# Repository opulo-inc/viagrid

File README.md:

# Viagrid
<br><br>

ViaGrid is a set of standardized PCB blank templates with pre-embedded vias in grid patterns, allowing for rapid 2 layer PCB prototyping and low-volume manufacturing, even at home. Instead of placing vias ad-hoc during routing, existing grid vias are assigned nets as needed and routed to in-place. Unused vias can remain part of the ground pour, orphaned by assigning an unused net, or converted to simple drilled holes. Viagrid blanks can be processed with a UV DPSS laser engravers, MLL machine and chemical etching, or with traditional CNC milling.<br><br>

> [!NOTE]
> Viagrid is still in development and is constantly evolving! If you wish to start creating PCBs based on a viagrid template who's status is not Complete in the table below, come and visit the #viagrid channel in the [Opulo Discord](https://discordapp.com/invite/TCwy6De) and ask for the latest version of the template you want to work with!
>
<br>**Currently, only the 9055 Standard blank is complete.** Other blank sizes and densities are planned:<br><br>

| Blank Name  | Status | Vias | Dimensions | Mounting ⌀ | Enclosure | Preview |
| ------------- | ------------- | ------------- | ------------- | ------------- | ------------- | ------------- |
| [ViaGrid 9055 Standard](https://github.com/opulo-inc/viagrid/tree/main/VIAGRID%20BLANK%20FILES/9055%20STANDARD) | Complete  | 180 | 90 x 55mm | Yes | Hammond 1591XXB Series | [Click Here](VIAGRID%20BLANK%20FILES/9055%20STANDARD/VIAGRID_9055_STANDARD.png) |
| ViaGrid 9055 Dense | Planned | TBD | 90 x 55mm | Yes | Hammond 1591XXB Series | Not Yet Available |
| [ViaGrid 6034 Standard](https://github.com/opulo-inc/viagrid/tree/main/VIAGRID%20BLANK%20FILES/6034%20STANDARD) | Complete | 82 | 60 x 34mm | Yes | Hammond 1551K/L Series | [Click Here](VIAGRID%20BLANK%20FILES/6034%20STANDARD/VIAGRID_6034_STANDARD.png) |
| ViaGrid 6034 Dense | Planned | TBD | 60 x 34mm | Yes | Hammond 1551K/L Series | Not Yet Available |
| ViaGrid Pi Hat | Planned | TBD | 65 x 56.5mm | Yes | Various Existing | Not Yet Available |
| ViaGrid Arduino Shield | Planned | TBD | 66.04 x 53.34mm | Yes | Various Existing | Not Yet Available |
| ViaGrid Guitar Pedal | Planned | TBD | 120 x 70mm | Yes | TBD | Not Yet Available |

<br>**Below is a preview of the ViaGrid 9055 Standard blank describing some quality of life features:**<br>
<br>

## Table of Contents
[File Prep](#file-prep)<br>
[Design](#design)<br>
[File Export](#file-export)<br>
[Fabrication Methods](#fabrication-methods)
<br><br>

When doing board layout, you drop your components onto the Viagrid template file. This shows you where the Viagrid blank already has vias embedded. When routing your board, simply drop your vias only where the Viagrid blank already has them.

When it comes time to fabricate your board, you only have to remove copper from the top and bottom layers, effectively deciding which net the vias are part of. This process can be done using UV DPSS lasers, chemical etching or CNC machining.

## File Prep

> [!NOTE]
> Viagrid has templates and instructions for only KiCAD and Eagle at the moment.

## Design

1. Design your schematic in KiCAD like you usually would. Assign footprints.
2. Before opening the .kicad_pcb file associated with your project, copy the `viagrid-template.kicad_pcb` file into your KiCAD project directory, and rename it to replace the default one.
3. Open the newly renamed `.kicad_pcb` file in KiCAD. The `User1` layer shows the location of the vias on the Viagrid blank, and the outer bounds of the usable area.
4. Set your board settings for best results:
   1. Vias: 1.5mm ring, 0.3mm drill
   2. Traces: no smaller than 0.2mm
   3. Copper pour: at least 0.3mm clearance
5. Route your board like you normally would.

## File Export

1. File -> Plot
2. When exporting, we only care about the front and back copper layers, and the front and back mask layers. Select these.
3. Export files as .DXF

## Fabrication Methods

[UV DPSS Laser Engraving](#uv-dpss-laser-engraving)<br>
[MLL & Chemical Etching](#chemical-etching)<br>
[CNC Machining](#cnc-machining)<br>
<br/>

### UV DPSS Laser Engraving

> [!WARNING]
> Lasers can damage or destroy your eyesight in milliseconds if you're not careful. Always wear certified, trustworthy eye protection MATCHED TO YOUR SPECIFIC LASER WAVELENGTH AND POWER and obtained from a reputable source such as ThorLabs when working with or around your laser. Keep all guards and protective filters in place when the laser is active, and follow all safe operating instructions provided by the manufacturer of your machine.

> [!WARNING]
> Lasers can ignite a surprising range of materials quickly and without warning, resulting in dangerous fires!  Never leave your laser unattended! Always keep a carbon dioxide fire extinguisher near your machine that's easily accessible!

Viagrid boards can be easily and autonomously cut using a UV DPSS (Diode Pumped Solid State) laser. These are commercially available and getting cheaper by the year. These instructions were prepared using a [Commarker Omni 1 (5W)](https://store.commarker.com/products/omni-1-uv-laser-engraver) however the same company has recently released a similar machine that is fully enclosed, called the [Omni X](https://store.commarker.com/products/omni-x-uv-laser-engraver).

> [!NOTE]
> We are asking a lot of this laser for this application. Any slight alignment error can result in inconsistent results across the work area.
> In my case, the laser galvo head was ever so slightly at an angle relative to the work area, which caused my cuts to be clean in one area, but barely work in others.
> To rectify this, I recommend barely loosening the three screws holding the galvo head onto the laser body, rotating the head until both sides are the same height from the work area, then tightening back down. I saw marked improvement to cutting performance after performing this adjustment.

#### Laser Prep

1. Print and assemble the alignment jig. Refer to the BOM in the relevant jig folder in this repository.
2. Mount to the laser base using M5x16mm bolts.
3. Mount a viagrid blank into the jig.
4. Connect the laser to your computer and follow manufacturer instructions for setup in Lightburn, including setting focus, scale, and Z-height.
5. Open the `viagrid.lbrn2` file in Lightburn.
6. Click the purple rectangle showing the outline of the viagrid copper pour (on layer 25).
7. Check `Output` next to layer 25, and then click the frame button.
8. Your laser should now be tracing this rectangle. Confirm that you see it tracing in a blue color. Use the visualization panel that comes with the laser if needed.
9. It's likely that the tracing is very far off from where the actual viagrid board is. If so, select the purple and brown rectangles and move them on the work area and frame again until you're within a few millimeters of the board's actual location.
10. Select the purple and brown rectangles, right click, and lock them.
11. Loosen the four gold thumbscrews on the alignment jig. You can now do fine adjustment to get the laser framing perfectly aligned with the Viagrid board. The board's corners are designed to have a small path of exposed FR4 that will illuminate when it's perfectly aligned. Adjust until you get all four corners of the Viagrid blank to light up, as shown below.

> [!NOTE]
> If you're feeling like it's impossible to get the rectangle perfectly illuminating in all four corners, it's likely you need to recalibrate your lens, or adjust the scale of your laser.

1.  Tighten down the thumbscrews.
2.  The alignment jig is now calibrated to your Viagrid lightburn job. Save the job and use this for all future etchings.

#### Running a job

1. Drop in top copper DXF file.
2. Make sure your imported board is the right size (90mm x 55mm)
3. Make inner bits layer 1, outer ring layer 30.
4. Group it.
5. Snap it onto locked outline.
6. Cut layer one with settings:

    - Speed: 100mm/s
    - Frequency: 35kHz
    - Q-Pulse Width: 1ns
    - Global Passes: 1
    - Mode: Fill
    - Line Interval (mm): 0.025
    - Scan Angle: 45deg
    - Number of Passes: 15
    - Angle Increment: 37deg
    - Fill all shapes at once: checked

7. Stop after layer one, and double check alignment. Are all your vias aligned with the traces?
8. Stop part way through and check, is your laser beefy and you're already done? Monitor the first job and how many passes you actually need to get through.
9. When done, remove from jig.
10. Sand down with 600 grit.
11. Inspect traces under a microscope and using a multimeter to ensure proper electrical isolation for all traces.

12. Put back in jig upside down
13. Get back copper in there, make sure it's flipped!
14. Cut the back side.

### Chemical Etching

<br>

#### Achieveable Results:
- *3mil traces.*
- *3mil spaces.*
- *Soldermask possible.*
- *Through-hole NOT possible without separate CNC mill.*
- *Flexible PCBs possible.*
- *Total average time from gerber to bare double-sided PCB: 20 minutes.*
- *Total average time from gerber to double-sided PCB with glossy soldermask (PET sheet): 25 minutes.*
- *Total average time from gerber to double-sided PCB with matte soldermask (tack dry): 90 minutes.*

#### *This documentation is a work in progress and is subject to change. Additional information and photos will be added over time.*

#### Overview

You don't have to be an electronics or chemical engineer to acid etch your own PCBs at home or small business. It's easy and safe if you are careful, if you can follow instructions and if you take your time. With that said:

> [!WARNING]
> Chemical etching of any PCB does require the use of certain chemicals which can be unsafe if not handled and disposed of properly. Generally, these will be FeCl3 (ferric chloride), NaOH (sodium hydroxide, commonly known as lye) and liquid tin. Do not mix chemicals, and always wear the proper PPE and follow all handling instructions recommended by the manufacturers of the equipment and chemicals you are using!

Na2CO3 (sodium carbonate) is also used, but is quite safe (it's basically just soda ash/powder laundry detergent).

Chemical etching of PCBs can be broken down into these steps:

- Create artwork masks for copper layers and place on UV photoresist-coated PCB (otherwise known as presensitized PCB).
- Expose UV photoresist-coated PCB to sufficient UV light for each copper layer to "burn" the artwork into the photoresist.
- Develop the PCB in diluted **Na2CO3** to remove areas of the photoresist coating, exposing the copper areas that we want to remove.
- Chemical etch the PCB in **FeCl3** to remove the copper areas that are now exposed after development.
- Strip the PCB of the rest of the photoresist coating in diluted **NaOH** to expose the copper.
- (Optional) Coat the PCB in UV soldermask on both sides.
- (Optional) Use a laser or follow UV artwork masking steps to tack dry and develop soldermask.
- (Optional) Repeat soldermask steps for more colors or to add silkscreen art.
- (Optional) Use HASL equipment or liquid tin to plate any exposed copper with a layer of tin or solder, to prevent corrosion and aid soldering.

> [!NOTE]
> When handling PCBs coated in UV photoresists or soldermasks, it is important to limit unintended exposure to UV as much as possible. It is recommended to work in a room lit with incandescent bulbs or white LED lighting. Sunlight, halogen bulbs and incandescent bulbs put out enough UV to cure photoresist in only a few minutes. For extended handling periods, it is recommended to install UV-free LED bulbs, such as the yellow "bug-free" bulbs that are generally available.

#### Photoresist and Artwork Masks

<br>

When chemically etching PCBs, a protective layer must exist over the copper areas we wish to keep. This is accomplished with a UV-sensitive acrylic polymer film, otherwise known as a UV photoresist. Both negative and positive photoresists exist. In simple terms, negative photoresist will "harden" when exposed to UV light, so the light must hit the areas of copper we wish to keep. Positive photoresist will "soften" when exposed to UV light, so the light must hit the areas of copper we wish to remove. Both types of coatings can achieve excellent detail and resolution if properly applied and exposed, and will never be the limiting factor for the quality of your DIY PCBs. Photoresist films are capable of tenting even large holes (>= ⌀5mm) and will easily protect the vias from etching.

Opulo-supplied Viagrid blanks can be used for chemical etching, but you must add this coating yourself, as they ship with ENIG plating and are intended primarily for use with laser etching.

A UV photoresist coating can be applied using standard UV photoresist films acquired from electronics suppliers or (less reliably) from markets such as Amazon, eBay and AliExpress. A thermal laminator and some patience is required for this method, but it can produce good results. Alternatively, aerosol-based spray cans of UV photoresist are also available, such as POSITIV 20. These are easier to apply, but cost significantly more, and require more care to get an even coating thickness. Ideally, you want a coating or film thickness of around 35µm. Almost all generally available photoresist coatings and films are negative photoresists, while most presensitized PCB blanks from vendors such as MG Chemicals and Kinsten are coated with a proprietary positive photoresist.

Typically, an artwork mask must be created for both copper layers (top and bottom) to sit between the UV photoresist coating and the PCB, which will block UV exposure to parts of the photoresist coating. Currently, this is the most difficult and error-prone step of chemically etching PCBs. Traditional DIY-friendly methods such as toner-transfer via printing on clear acetate or vellum sheets are prone to defects and misalignments, and can limit feature sizes and detail.

Once the artwork masks are created, we must place them on the PCB. It is easiest to do both layers separately, starting with the top copper layer and artwork mask. Place the artwork mask on top of the PCB and ensure it is aligned and as flat as possible. Markings on the edge rails and the vias embedded into the Viagrid blanks will greatly assist with alignment. **Make sure you use the correct mask for the intended layer to be exposed, and that it's not flipped upside down or rotated incorrectly! Viagrid includes helpful indicators on the edge rails to identify the top and bottom sides and orientation.**

> [!NOTE]
> Viagrid blanks which are shipped pre-coated with negative UV photoresist and ready for immediate use with chemical etching are in late-stage development. Several hundred have already been produced. A purpose-built, open source masking and exposure machine based on SLA (stereolithography) and targeted at hobbyists and makers is currently also in late stage development. Several prototype machines are nearing completion - please tag @MatinatorX in the Opulo Discord server if you are interested in helping or testing.

#### UV Exposure

<br>

With the top copper layer mask artwork in place and aligned, the PCB can now be exposed to UVA light (ideally 395-405nm wavelength) to "burn" the artwork into the photoresist. The source of UV light can be just about anything, including the sun - however, underexposure, overexposure and uneven exposure can lead to more difficulty during the development steps, areas of the board which cannot be developed, uneven feature thicknesses or portions of photoresist coming off the board which should have remained. As such, it is recommended to use a controlled UV light source on a timer, so a repeatable and adjustable amount of even UV exposure can be achieved. The ideal exposure time and intensity can be found in the TDS (technical datasheet) for your chosen photoresist. However, as a general rule, for a 35µm negative photoresist, around 60 seconds of exposure with a 5W UVA source located 15cm away from the PCB is a good place to start.

Switch to the backside of your Viagrid blank and repeat this process for the bottom copper layer of the PCB, again ensuring the artwork mask is oriented correctly and not flipped.

#### Development

<br>

Once both sides have been exposed, remove the artwork masks from the Viagrid PCB. We are now ready to develop the PCB, which for most negative resists is done with a 1% Na2CO3 (sodium carbonate) to warm water solution. (For positive resists, follow the manufacturer instructions.) There are various ways to do this, but we will go over the most accessible method here:

- Find a small waterproof container big enough for your Viagrid PCB and place it on a small scale (plastic tupperware is a good choice).
- Tare or zero the scale, so the container weight is now ignored.
- Fill the container halfway with warm water (30°C is ideal) and make a note of the weight on the scale (eg: 500g).
- Tare or zero the scale, so the water and container weight is now ignored.
- Slowly add in the sodium carbonate until the scale shows 1% of the weight of the water (eg: 5g).
- Stir the solution until the sodium carbonate is dissolved.
- Place your exposed Viagrid PCB in the solution and let soak for 30 seconds.
- Using a very mildly abrasive object such as a foam sponge, gently scrub the board to remove the unexposed photoresist.
- Flip over the Viagrid PCB and let soak for 30 seconds, then repeat previous step.
- Rinse board under cold tap and dry with compressed or gently via paper towel (DO NOT SCRUB as this may remove photoresist defining fine features).

We are now ready to etch the board!

#### Etching

<br>

There are various chemicals which can be used to etch PCBs, but the most common and flexible is FeCl3 (ferric-chloride), with the main downside being it will stain your skin orange for a while if you do get some on you (wash your skin properly right away if this happens - it is an acid after all!)

The most accessible method of DIY etching is the sponge method detailed here:<br>
https://www.instructables.com/Sponge-Ferric-Chloride-Method-Etch-Circuit-Bo/

For more automated and faster etching, it is recommended to purchase a bubble etcher such as this rebranded Kinsten ET20:<br>
https://www.circuitspecialists.com/et20

In both cases, etching of both sides of the Viagrid PCB can be achieved in under 10 minutes with fresh FeCl3. The small remaining amount of FeCl3 on the PCB after etching should be removed with paper towel. Once dry, the very small amount on the paper towel is safe to dispose of with regular garbage.

> [!NOTE]
> FeCl3 loses it's effectiveness over time as it becomes saturated with dissolved copper and must be periodically replaced. **DO NOT POUR FERRIC CHLORIDE DOWN THE DRAIN OR OTHERWISE DISPOSE OF IMPROPERLY, ESPECIALLY USED FERRIC CHLORIDE.** Store it in an appropriate container and bring it to your local hazardous waste center - it's generally free for individuals and is sent for recycling.

#### Stripping

<br>

The process of removing the "hardened" UV photoresist is very similar to the development steps, but with 1% NaOH (sodium hydroxide/lye) to cold water solution.

> [!WARNING]
> NaOH (sodium hydroxide/lye) can cause thermal and chemical burns and dangerous vapors even in low concentrations. Higher concentrations (>=2-3%) can heat up enough to melt plastic containers and scar metals. Again, always wear the proper PPE and follow all handling instructions recommended by the manufacturers of the equipment and chemicals you are using!

Again, there are various ways to do this, but we will go over the most accessible method here:

- Find a small waterproof and heat resistant container big enough for your Viagrid PCB and place it on a small scale (glass tupperware is a good choice).
- Tare or zero the scale, so the container weight is now ignored.
- Fill the container halfway with cold water (10°C is ideal) and make a note of the weight on the scale (eg: 500g).
- Tare or zero the scale, so the water and container weight is now ignored.
- Slowly add in the sodium hydroxide until the scale shows 1% of the weight of the water (eg: 5g).
- Stir the solution with a non-metallic stirrer until the sodium hydroxide is dissolved. This process will heat up the mixture significantly.
- Place your exposed Viagrid PCB in the solution and let soak until the "hardened" photoresist falls off, typically 2-3 minutes.
- Rinse the board under a cold tap. (Uncontaminated sodium hydroxide in low concentrations is safe to dispose of down a household drain - it's most typical use is as a drain cleaner after all.)
- Pour the sodium hydroxide mixture through a plastic strainer to separate out the "hardened" photoresist.
- The sodium hydroxide can now be safely disposed of down a household drain. The "hardened" photoresist can be disposed of with regular garbage once dried.

Congratulations, you now have a complete, shiny, bare PCB ready to use! Any exposed copper will oxidize quickly, so it is recommended to continue on to the soldermask steps immediately if soldermask is desired, or to immediately dip the board in liquid tin to plate and protect the exposed copper. This will also provide a better soldering experience.

#### Soldermask & Silkscreen

<br>

A soldermask jig and process specific for Viagrid blanks is in late-stage development, which keeps your fingers clean and provides high quality results.

Soldermask can be removed via laser or developed similar to the UV photoresist.

#### *The rest of this section is a work in progress.*

#### Liquid Tin

<br>

The recommended brand of liquid tin is MG Chemicals 421A:<br>
https://mgchemicals.com/products/circuit-board-design/electroless-plating/421a-liquid-tin/

> [!WARNING]
> **421A is corrosive and can cause severe skin burns and eye damage. Again, always wear the proper PPE and follow all handling instructions recommended by the manufacturers of the equipment and chemicals you are using!**

It only takes a few minutes dipped in 421A to get a nice thick layer of tin on your copper surfaces:

### CNC Machining

#### *This section is a work in progress. Please let us know if you want to help!*

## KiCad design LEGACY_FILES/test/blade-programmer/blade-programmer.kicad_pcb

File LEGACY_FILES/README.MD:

This directory contains the working PCB, jig and configuration files for the initial commit of ViaGrid. Many of these files are considered depreciated and were relocated here for archival purposes.

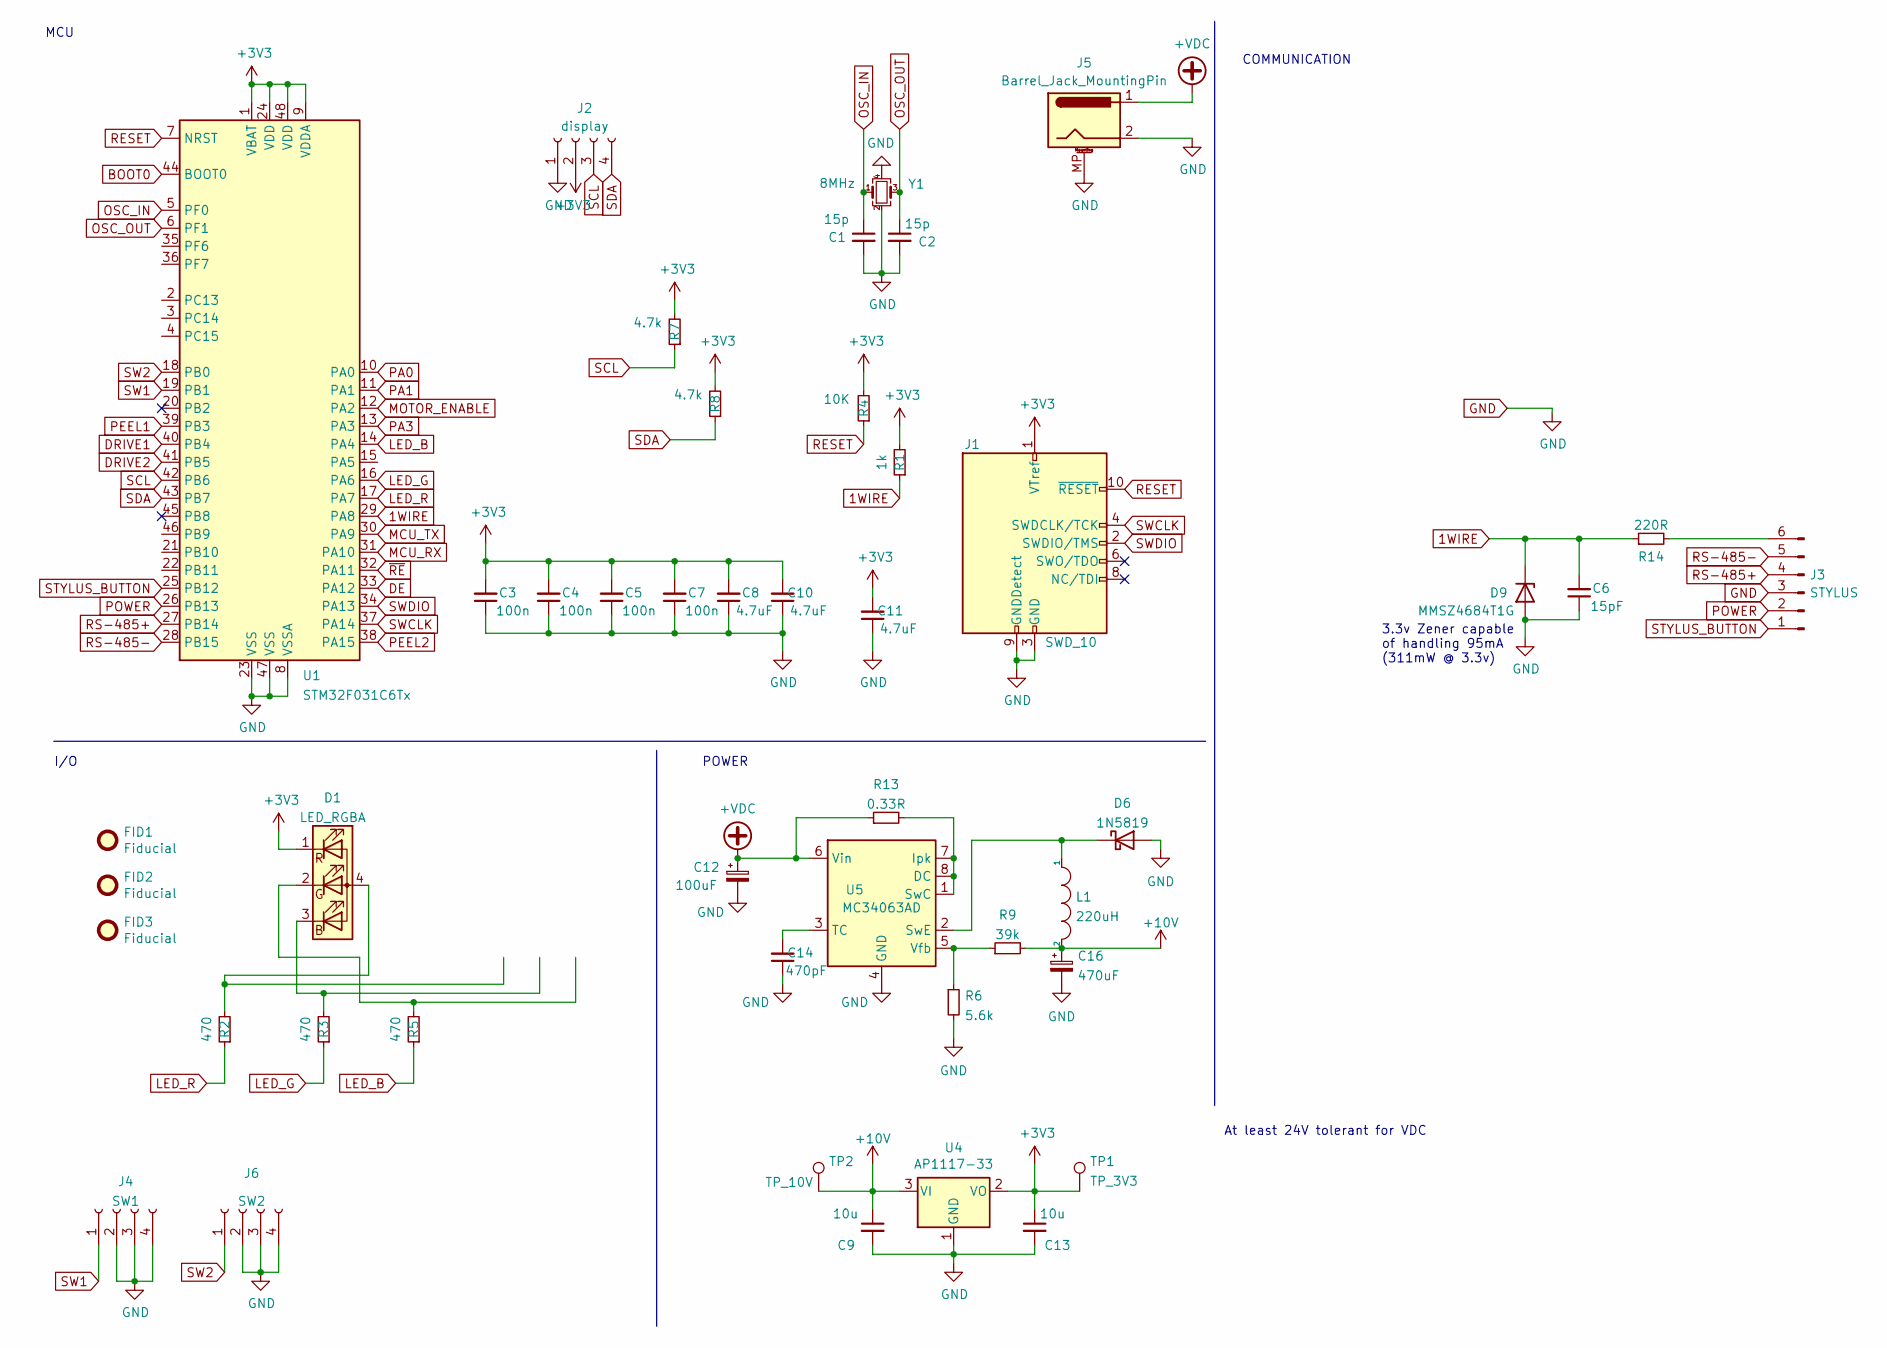
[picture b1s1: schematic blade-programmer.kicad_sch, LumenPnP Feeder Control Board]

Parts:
C1, C2: 15p; C_0805_2012Metric; JLCPCB C1794
C3, C4, C5, C7: 100n; C_0805_2012Metric; JLCPCB C49678
C6: 15pF; C_0805_2012Metric; JLCPCB C49678
C8, C10, C11: 4.7uF; C_0805_2012Metric; JLCPCB C49678
C9, C13: 10u; C_0805_2012Metric; JLCPCB C15850
C12: 100uF; C_Elec_6.3x7.7
C14: 470pF; C_0805_2012Metric; JLCPCB C49678
C16: 470uF; C_Elec_6.3x7.7
D1: LED_RGBA; MHS110FRGBCT
D6: 1N5819; D_SOD-123
D9: MMSZ4684T1G; D_SOD-123; JLCPCB MMSZ4684T1G
FID1, FID2, FID3: Fiducial; Fiducial_1mm_Mask2mm
J1: SWD_10; PinHeader_2x05_P1.27mm_Vertical_SMD
J2: display; PinHeader_1x04_P2.54mm_Vertical
J3: STYLUS; JST_PH_B6B-PH-SM4-TB_1x06-1MP_P2.00mm_Vertical
J4: SW1; SW_SPST_B3S-1000; LCSC C319392
J5: Barrel_Jack_MountingPin; BarrelJack_Horizontal
J6: SW2; SW_SPST_B3S-1000; LCSC C319392
L1: 220uH; L_6.3x6.3_H3; LCSC C467145
R1: 1k; R_0805_2012Metric; JLCPCB C17513
R2, R3, R5: 470; R_0805_2012Metric; JLCPCB C17710
R4: 10K; R_0805_2012Metric; JLCPCB C17513
R6: 5.6k; R_0805_2012Metric
R7, R8: 4.7k; R_0805_2012Metric; JLCPCB C17513
R9: 39k; R_0805_2012Metric
R13: 0.33R; R_0805_2012Metric
R14: 220R; R_0805_2012Metric
TP1: TP_3V3; TestPoint_Pad_D2.0mm
TP2: TP_10V; TestPoint_Pad_D2.0mm
U1: STM32F031C6Tx; LQFP-48_7x7mm_P0.5mm
U4: AP1117-33; SOT-223-3_TabPin2; JLCPCB C108785
U5: MC34063AD; SOIC-8_3.9x4.9mm_P1.27mm
Y1: 8MHz; Crystal_SMD_3225-4Pin_3.2x2.5mm_HandSoldering; JLCPCB C253751

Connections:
1WIRE: C6.2, D9.1 (K), R1.1, R14.1, U1.29 (PA8)
+3V3: C3.2, C4.2, C5.2, C7.2, C8.2, C10.2, C11.2, C13.1, D1.1 (RK), J1.1 (VTref), J2.2, R1.2, R4.2, R7.2, R8.2, TP1.1, U1.1 (VBAT), U1.9 (VDDA), U1.24 (VDD), U1.48 (VDD), U4.2 (VO)
+10V: C9.1, C16.1, L1.2, R9.2, TP2.1, U4.3 (VI)
+VDC: C12.1, J5.1, R13.1, U5.6 (Vin)
BOOT0: U1.44 (BOOT0)
DE: U1.33 (PA12)
DRIVE1: U1.40 (PB4)
DRIVE2: U1.41 (PB5)
GND: C1.2, C2.2, C3.1, C4.1, C5.1, C6.1, C7.1, C8.1, C9.2, C10.1, C11.1, C12.2, C13.2, C14.1, C16.2, D6.2 (A), D9.2 (A), J1.3 (GND), J1.5 (GND), J1.9 (GNDDetect), J2.1, J3.3, J4.2, J4.3, J4.4, J5.2, J5.MP (MountPin), J6.2, J6.3, J6.4, R6.2, U1.8 (VSSA), U1.23 (VSS), U1.47 (VSS), U4.1 (GND), U5.4 (GND), Y1.2, Y1.4
LED_B: R5.1, U1.14 (PA4)
LED_G: R3.1, U1.16 (PA6)
LED_R: R2.1, U1.17 (PA7)
MCU_RX: U1.31 (PA10)
MCU_TX: U1.30 (PA9)
MOTOR_ENABLE: U1.12 (PA2)
unnamed: D1.4 (A), R2.2
unnamed: D1.3 (BK), R3.2
unnamed: D1.2 (GK), R5.2
unnamed: D6.1 (K), L1.1, U5.2 (SwE)
unnamed: J3.6, R14.2
unnamed: R13.2, U5.1 (SwC), U5.7 (Ipk), U5.8 (DC)
unnamed: C14.2, U5.3 (TC)
unnamed: R6.1, R9.1, U5.5 (Vfb)
OSC_IN: C1.1, U1.5 (PF0), Y1.1
OSC_OUT: C2.1, U1.6 (PF1), Y1.3
PA0: U1.10 (PA0)
PA1: U1.11 (PA1)
PA3: U1.13 (PA3)
PEEL1: U1.39 (PB3)
PEEL2: U1.38 (PA15)
POWER: J3.2, U1.26 (PB13)
RESET: J1.10 (~RESET), R4.1, U1.7 (NRST)
RS-485+: J3.4, U1.27 (PB14)
RS-485-: J3.5, U1.28 (PB15)
SCL: J2.3, R7.1, U1.42 (PB6)
SDA: J2.4, R8.1, U1.43 (PB7)
STYLUS_BUTTON: J3.1, U1.25 (PB12)
SW1: J4.1, U1.19 (PB1)
SW2: J6.1, U1.18 (PB0)
SWCLK: J1.4 (SWDCLK/TCK), U1.37 (PA14)
SWDIO: J1.2 (SWDIO/TMS), U1.34 (PA13)
~RE: U1.32 (PA11)

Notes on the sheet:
I/O
COMMUNICATION
POWER
3.3v Zener capable of handling 95mA (311mW @ 3.3v)
At least 24V tolerant for VDC
MCU

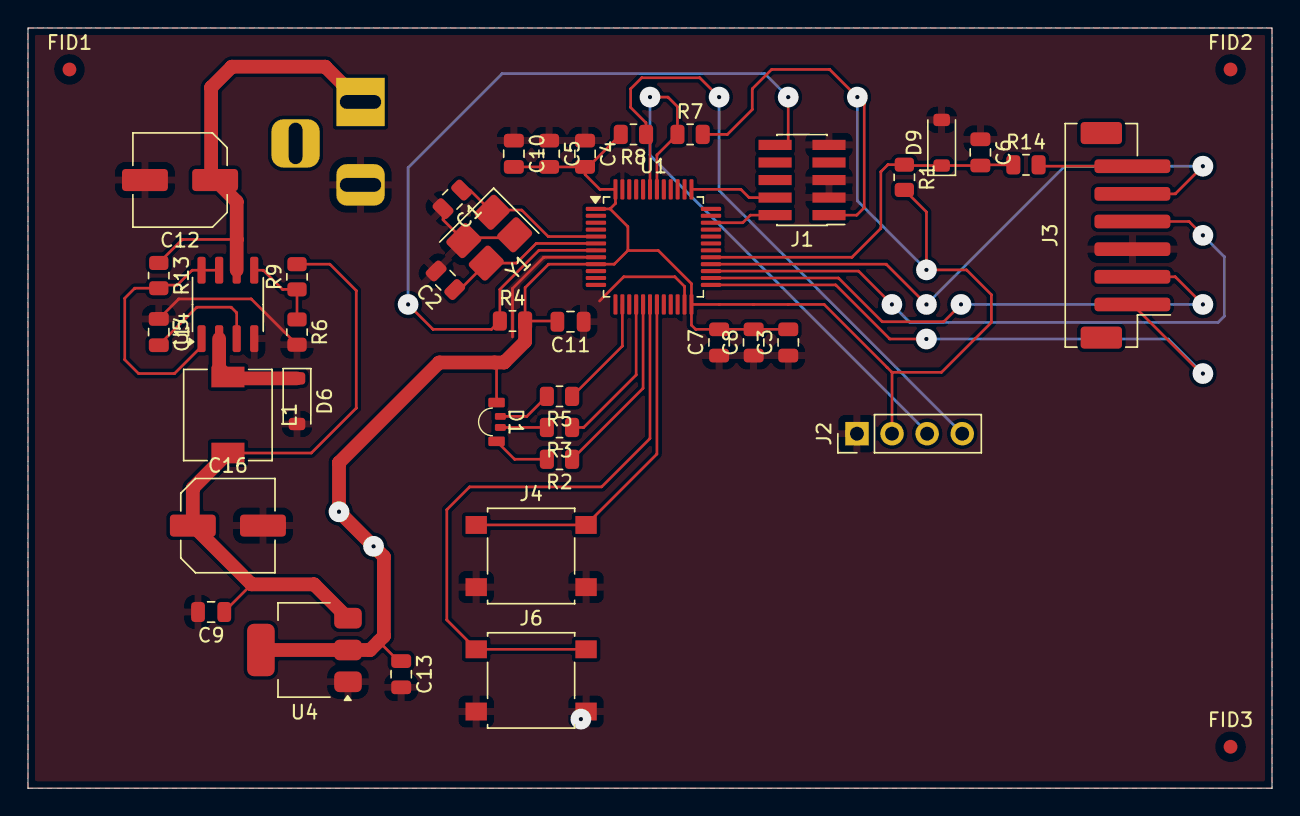
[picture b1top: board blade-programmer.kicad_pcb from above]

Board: 2 copper layers, 90.0 x 55.0 mm, 43 parts (1 on the bottom side), 29 nets.

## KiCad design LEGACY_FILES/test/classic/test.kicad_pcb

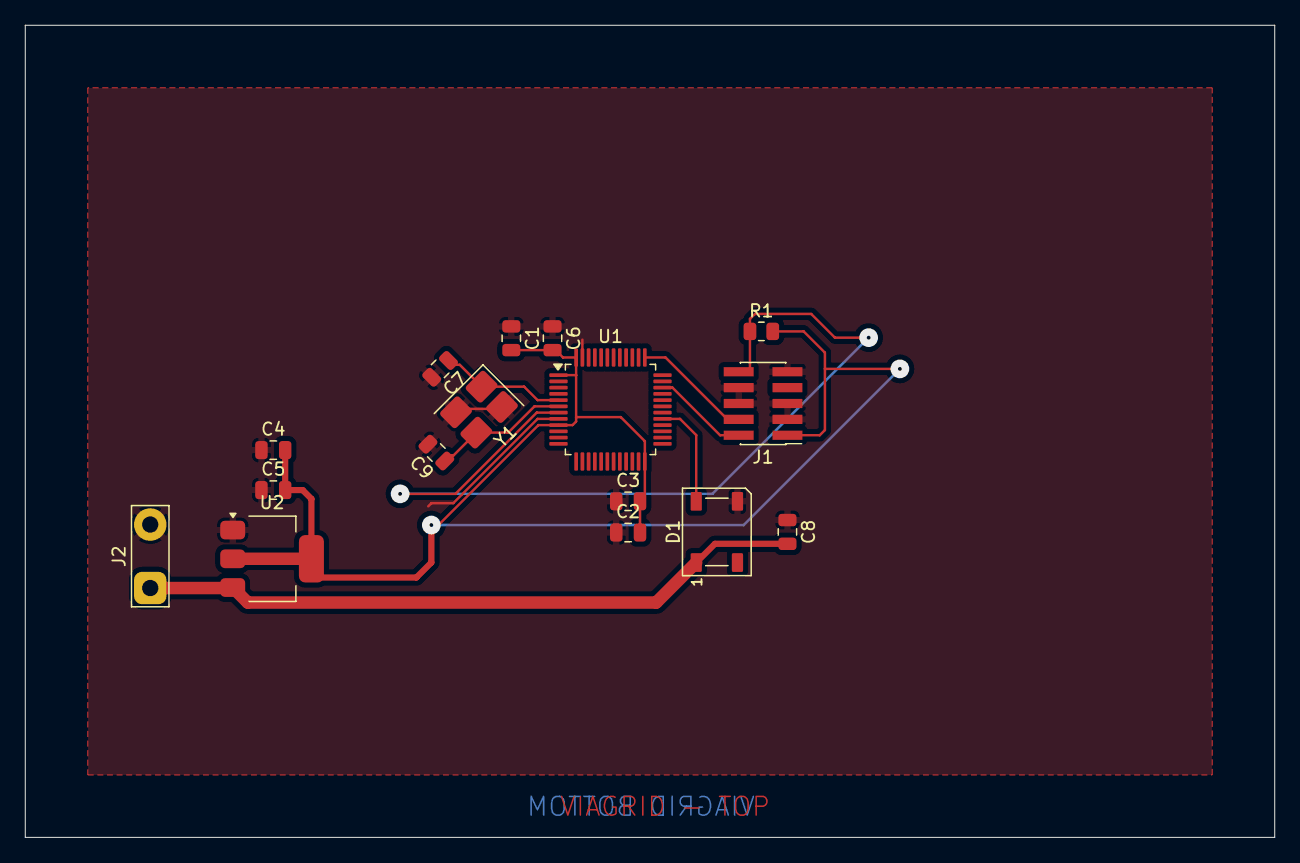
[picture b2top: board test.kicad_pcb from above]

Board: 2 copper layers, 100.0 x 65.0 mm, 16 parts (0 on the bottom side), 9 nets.

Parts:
C1, C2, C3, C4: 100n; C_0805_2012Metric
C5, C6, C8: 4.7uF; C_0805_2012Metric
C7, C9: 15p; C_0805_2012Metric
D1: WS2812B; LED_WS2812B_PLCC4_5.0x5.0mm_P3.2mm
J1: SWD_10; PinHeader_2x05_P1.27mm_Vertical_SMD
J2: PWR; TestPoint_2Pads_Pitch5.08mm_Drill1.3mm
R1: 10K; R_0805_2012Metric
U1: STM32F031C6Tx; LQFP-48_7x7mm_P0.5mm
U2: AZ1117-3.3; SOT-223-3_TabPin2
Y1: 8MHz; Crystal_SMD_3225-4Pin_3.2x2.5mm_HandSoldering

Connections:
+3V3: C1.2, C2.2, C3.2, C4.2, C5.2, C6.2, J1.1 (VTref), R1.2, U1.1 (VBAT), U1.9 (VDDA), U1.24 (VDD), U1.48 (VDD), U2.2 (VO)
+5V: C8.2, D1.1 (VDD), J2.1, U2.3 (VI)
DATA: D1.4 (DIN), U1.29 (PA8)
GND: C1.1, C2.1, C3.1, C4.1, C5.1, C6.1, C7.2, C8.1, C9.2, D1.3 (VSS), J1.3 (GND), J1.5 (GND), J1.6 (SWO/TDO), J1.8 (NC/TDI), J1.9 (GNDDetect), J2.2, U1.8 (VSSA), U1.23 (VSS), U1.47 (VSS), U2.1 (GND), Y1.2, Y1.4
OSC_IN: C7.1, U1.5 (PF0), Y1.1
OSC_OUT: C9.1, U1.6 (PF1), Y1.3
RESET: J1.10 (~RESET), R1.1, U1.7 (NRST)
SWCLK: J1.4 (SWDCLK/TCK), U1.37 (PA14)
SWDIO: J1.2 (SWDIO/TMS), U1.34 (PA13)

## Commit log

2025-10-27 Fix typo in README.md
2025-11-01 Add WIP note and laser safety warnings to README.md
2025-11-01 Better wording for laser warnings.
2025-11-01 Typo fix.
2025-11-01 More safety warnings.
2025-11-14 Add $.lck to .gitignore
2025-11-14 Delete PCB/viagrid/~viagrid.kicad_pcb.lck
    To avoid slowdowns and the warning that the file is open by someone else.
2025-11-14 Update .gitignore to include lock files
    Typo
2025-12-08 Add logo
2025-12-08 Replace viagrid logo
2025-12-08 Replace logo again
2025-12-08 Update README.md with logo
2025-12-08 Add ViaGrid_9055_Standard image.
2025-12-08 Organization
2025-12-08 feat: :sparkles: add KiCad version
2025-12-08 Finish cleaning up repo.
2025-12-08 Fix typo.
2025-12-08 Better wording.
2025-12-10 Move files to MANUFACTURING folder.
2025-12-10 feat: :fire: remove unnecessary placeholder files
2025-12-23 Fixed typo
2026-02-01 Remove extraneous HTML tags in README.md
2026-02-01 Update README.md
    Fix unclosed bold tag.
2026-02-01 Update README.md
    Fix another unclosed bold tag.
2026-02-01 Update README.md
    Replace bold tags with markdown formatting.
2026-03-28 Add PROCESS_TESTS folders.
2026-03-28 Add 9055 test gerbers.
2026-03-28 Add process tests documentation.
2026-04-04 Add ViaGrid 6034 Info
2026-04-04 Finish ViaGrid 6034 Standard
2026-04-04 Fix upload.
2026-04-04 Remove wrong file.
2026-04-04 Fix older version.
